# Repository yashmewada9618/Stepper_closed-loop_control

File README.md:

# Stepper_closed-loop_control
Stepper motor with as5600 magnetic encoder control system
These examples contain all the iterations tried to make a stepper motor absolute closed loop system with magnetic encoder and DRV8825/A4988 stepper motor driver.

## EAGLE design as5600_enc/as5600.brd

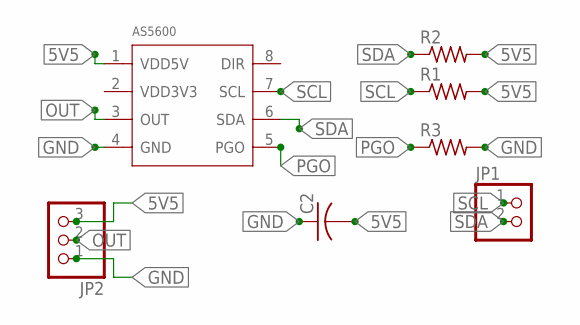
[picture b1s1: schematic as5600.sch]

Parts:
AS5600: AS5600AS5600; AS5600
C2: C-USC0603; C0603
JP1: PINHD-1X2; 1X02
JP2: PINHD-1X3; 1X03
R1, R2, R3: R-US_R0603; R0603

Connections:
5V5: AS5600.1 (VDD5V), C2.2, JP2.3, R1.2, R2.2
GND: AS5600.4 (GND), C2.1, JP2.1, R3.2
OUT: AS5600.3 (OUT), JP2.2
PGO: AS5600.5 (PGO), R3.1
SCL: AS5600.7 (SCL), JP1.1, R1.1
SDA: AS5600.6 (SDA), JP1.2, R2.1

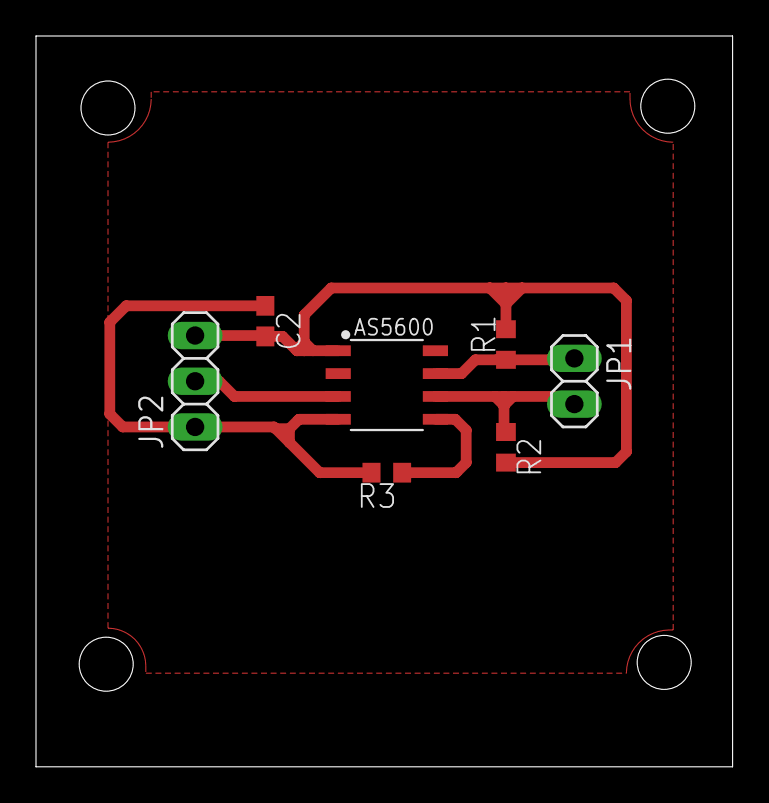
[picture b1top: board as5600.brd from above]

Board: 2 copper layers, 38.7 x 40.6 mm, 7 parts (0 on the bottom side), 6 nets.
